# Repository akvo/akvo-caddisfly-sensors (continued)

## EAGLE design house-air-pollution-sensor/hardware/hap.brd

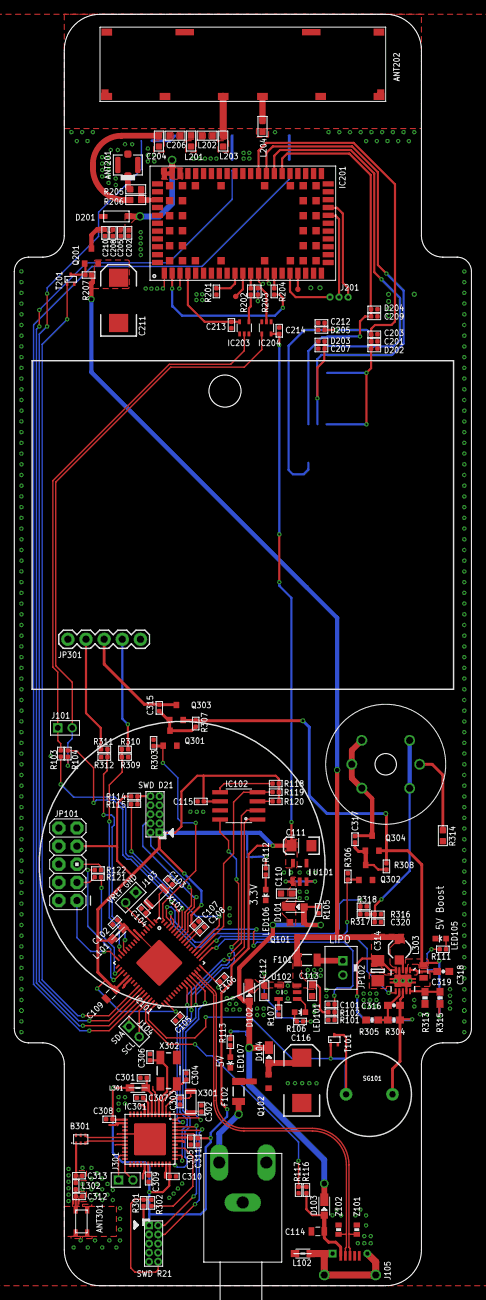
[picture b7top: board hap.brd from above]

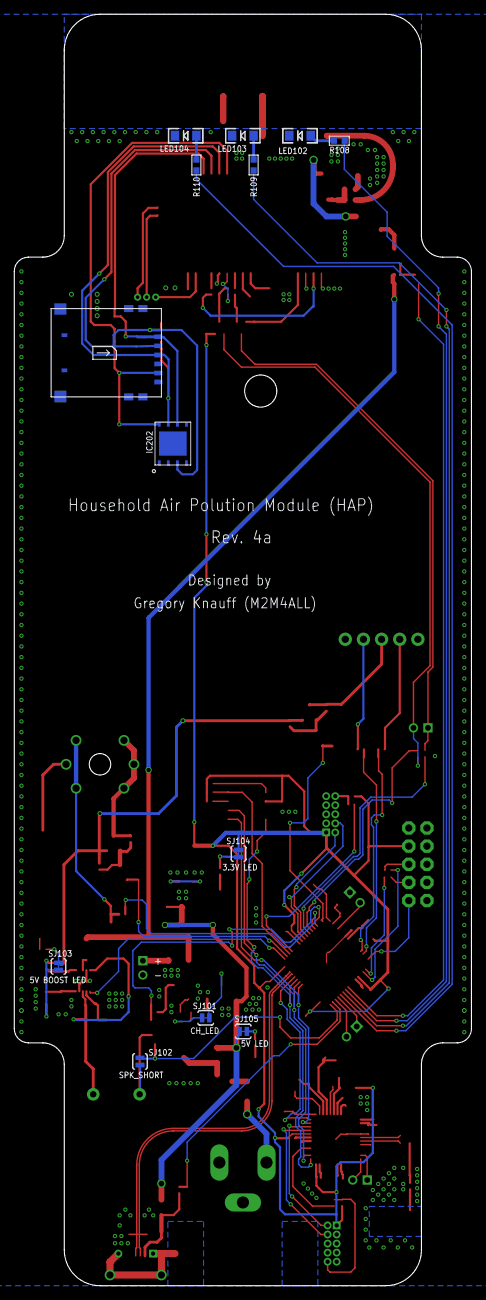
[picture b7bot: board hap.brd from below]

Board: 2 copper layers, 64.0 x 178.0 mm, 174 parts (13 on the bottom side), 124 nets.

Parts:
ANT201: 4P-U-FL
ANT202: A10393 (N.C.); A10393
ANT301: 2450AT18D0100
B301: BALUN
C101, C102, C105, C106, C107, C108, C115, C201, C210, C213, C214, C301, C305, C307, C308, C309, C310, C311, C320: 100nF; C0402
C103, C104, C202, C302, C303, C304, C306: 15pF; C0402
C109, C114, C319: 22uF; 0805
C110: 1uF; C0603
C111: 100uF; EIA3216
C112, C113: 4.7uF; C0603
C116, C211: 330uF; EIA7343
C203, C207, C209, C212: 47pF; C0402
C204: 33pF 5% (N.C.); C0603
C205: 56pF; C0402
C206: 2.2pF (+-0.1pF)(N.C.); C0603
C208: 10nF; C0402
C312: 22pF; C0402
C313: 1.2pF; C0402
C314: 10uF; 1206
C315, C317: 1uF; C0402
C316, C318: 100nF; 0603-CAP
CN101, CN301: PINHEAD-2x5-P1.27; PINHEAD_2X05_127
D101, D102, D103, D104: MSS1P2L; D1005
D201: MMSZ5231BT1G; SOD-123
D202, D203, D204, D205: PESD0402-140; R0402
F101: 0R; PTC-1206
F102: PTCSMD; PTC-1206
IC101: ATSAMD21J18-MU; QFN64
IC102: AT45DB161E; SO08
IC201: UBLOX_SARA_U2STANDARD; SARA-U2
IC202: SIM_CHIP; DFN8
IC203, IC204: 74LVC1G125DCK; SC70-5
IC301: ATSAMR21G18; QFN48_SMALL-CPAD
J101, J103, J104, J301: 2P-2.0
J105: ZX62D-B-5P8
J106: DC-005; 712-22-23_RA
J201: 1X03_1.27MM; 1X03_1.27MM_NOSILK
JP101: M05X2PTH; AVR_ICSP
JP102: JST_EPH_2PIN; JST_EPH_B2B-PH-K-S
JP301: 1X05
L101, L102, L301: MH2029-300Y; 0805
L201: 10nH 5% (N.C.); R0603
L202: 3.3nH (+-0.3nH)(N.C.); R0603
L203: N.C.; R0603
L204: 0R (N.C.); R0603
L302: 1.8nH; L0402
L303: 4.7uH, 1.2A; CDRH2D09
LED101: Yellow; LED-0603
LED102, LED103: Yellow; LED-1206
LED104: Green; LED-1206
LED105, LED106, LED107: Red; LED-0603
Q101, Q102, Q201, Q303, Q304: FDN340P; SOT23-S-PADS
Q301, Q302: 2N7002; SOT23-S-PADS
R101, R117: 4.7M; R0402
R102: 10M; R0402
R103, R106, R111, R112, R113: 1k; R0402
R104: 33R; R0402
R105, R114, R118, R119, R120, R204, R301: 100k; R0402
R107: 2k; R0402
R108, R109, R110: 220R; R0603
R115, R302: 330R; R0402
R116: 3M; R0402
R121, R122, R201, R202, R203: 0R; R0402
R205: 0R; R0603
R206: 0R (N.C.); R0603
R207, R303, R306, R307, R308: 10k; R0402
R304, R315: 2M; 0603-RES
R305, R313: 220k; 0603-RES
R309, R311, R317: 1M; R0402
R310, R312, R318: 2M; R0402
R314: 5R1; R0603
R316: 1k (DNP); R0402
SENS301: METHANE_SENSOR; MQ-3
SG101: BUZZERPTH; BUZZER-12MM
SJ101, SJ103, SJ104, SJ105: SOLDERJUMPER_NC; SJ_2S_NC
SJ102: SOLDERJUMPER_NO; SJ_2S_NO
T101, T201: DTC114YE; SC-75-3
TP1, TP2: TEST-POINT3; PAD.03X.03
U101: XC6220; SOT23-5
U102: MCP73831; SOT23-5
U201: MICRO-SIM
U301: TPS61200; QFN-10_PAD
X101, X301: 32.768 kHz; 2P-SMD-3.2X1.5
X302: 16MHz; CRYSTAL-SMD-5X3
Z101, Z102: CG0402MLC-05LG; 0402-RES

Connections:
1.8V: C213.2, IC201.4, IC203.5
3.3V: C105.2, C106.2, C107.2, C109.2, C111.A, C115.2, C214.2, C305.2, C308.2, C310.2, CN101.1, CN301.1, IC101.21, IC101.34, IC101.48, IC101.56, IC102.6, IC204.5, IC301.13, IC301.36, IC301.44, JP101.7, L101.2, L301.2, R114.1, R118.2, R119.2, R120.2, R301.1, SJ104.2, U101.5
5V: D101.+, D102.+, D103.-, D104.-, Q101.1, R105.2, SJ105.2
5V_EN: IC101.49, U301.6
+5V: C319.1, Q303.2, Q304.2, R307.2, R308.2, R315.2, SJ103.2, U301.2
BAT_VOLT: C101.2, IC101.62, R101.1, R102.2
CO2_AOUT: IC101.16, JP101.1
CO_AOUT: IC101.61, R317.2, R318.1
CO_SW: IC101.50, Q302.1, R306.2
FB: R313.2, R315.1, U301.10
GND: ANT201.GND1, ANT201.GND2, ANT201.GND3, ANT301.2, ANT301.3, ANT301.4, B301.2, B301.5, B301.6, C101.1, C102.2, C103.1, C104.2, C105.1, C106.1, C107.1, C108.1, C109.1, C110.1, C111.C, C112.2, C113.2, C114.2, C115.1, C116.C, C201.1, C202.1, C203.1, C204.2, C205.1, C207.1, C208.1, C209.1, C210.1, C211.C, C212.1, C213.1, C214.1, C301.2, C302.1, C303.2, C304.2, C305.1, C306.2, C307.2, C308.1, C309.2, C310.1, C311.2, C312.2, C313.2, C314.2, C318.2, C319.2, C320.2, CN101.3, CN101.5, CN101.9, CN301.3, CN301.5, CN301.9, D201.A, D202.2, D203.2, D204.2, D205.2, IC101.0, IC101.7, IC101.22, IC101.33, IC101.47, IC101.54, IC102.7, IC201.1, IC201.3, IC201.5, IC201.14, IC201.20, IC201.21, IC201.22, IC201.30, IC201.32, IC201.33, IC201.43, IC201.50, IC201.54, IC201.55, IC201.57, IC201.58, IC201.59, IC201.60, IC201.61, IC201.63, IC201.64, IC201.65, IC201.66, IC201.67, IC201.68, IC201.69, IC201.70, IC201.71, IC201.72, IC201.73, IC201.74, IC201.75, IC201.76, IC201.77, IC201.78, IC201.79, IC201.80, IC201.81, IC201.82, IC201.83, IC201.84, IC201.85, IC201.86, IC201.87, IC201.88, IC201.89, IC201.90, IC201.91, IC201.92, IC201.93, IC201.94, IC201.95, IC201.96, IC202.1, IC203.1, IC203.3, IC204.1, IC204.3, IC301.0, IC301.5, IC301.8, IC301.14, IC301.17, IC301.20, IC301.29, IC301.35, IC301.42, J103.1, J105.P$5, J106.SLEEVE, J106.SLEEVE_SHUNT, JP101.9, JP102.2, JP301.5, L102.1, L201.2, L203.2, L204.1, LED102.C, LED103.C, LED104.C, LED105.C, LED106.C, LED107.C, Q102.1, Q301.2, Q302.2, R102.1, R105.1, R107.2, R117.2, R201.2, R303.1, R305.1, R306.1, R310.2, R312.2, R313.1, R314.1, R316.1, R318.2, T101.2, T201.2, U101.2, U102.2, U201.C5, U201.GND@0, U201.GND@1, U201.GND@2, U201.GND@3, U201.GND@4, U201.GND@5, U301.4, U301.9, U301.11, U301.12, U301.13, U301.14, U301.15, Z101.1, Z102.1
LED1: IC101.26, R108.1
LED2: IC101.27, R109.1
LED3: IC101.28, R110.1
LIPO_STAT: LED101.C, U102.1
MISO: IC101.43, IC102.8, IC301.37
MOSI: IC101.41, IC102.1, IC301.47
unnamed: IC102.5, R118.1
unnamed: LED104.A, R110.2
unnamed: ANT301.1, C312.1, L302.1
unnamed: LED103.A, R109.2
unnamed: IC102.3, R120.1
unnamed: IC301.24, J301.2
unnamed: B301.1, C313.1, L302.2
unnamed: IC301.23, J301.1
unnamed: IC201.56, R205.2, R206.1
unnamed: F101.2, JP102.1
unnamed: C110.2, D101.-, Q101.2, U101.1, U101.3
unnamed: ANT201.D, R205.1
unnamed: LED101.A, R106.2
unnamed: R107.1, U102.5
unnamed: C112.1, D102.-, SJ101.2, U102.4
unnamed: R106.1, SJ101.1
unnamed: C204.1, C206.1, R206.2
unnamed: B301.4, IC301.18
unnamed: B301.3, IC301.19
unnamed: C206.2, L201.1, L202.1
unnamed: IC201.15, R204.1
unnamed: IC201.2, R204.2
unnamed: Q201.1, R207.2, T201.3
unnamed: IC201.10, R201.1
unnamed: IC201.11, TP1.P$1
unnamed: IC201.18, TP2.P$1
unnamed: IC201.13, R203.1
unnamed: IC201.12, R202.1
unnamed: ANT202.1, L202.2, L203.1
unnamed: C202.2, C205.2, C208.2, C210.2, D201.C, IC201.51, IC201.52, IC201.53, Q201.3
unnamed: ANT202.2, L204.2
unnamed: R314.2, SENS301.HB
unnamed: LED102.A, R108.2
unnamed: L303.P$1, U301.3
unnamed: C318.1, U301.1
unnamed: JP101.5, R122.2
unnamed: JP101.3, R121.1
unnamed: LED105.A, R111.2
unnamed: LED106.A, R112.2
unnamed: LED107.A, R113.2
unnamed: SG101.-, SJ102.1, T101.3
unnamed: IC101.32, SJ102.2, T101.1
unnamed: F102.1, J106.CENTER_PIN
unnamed: C114.1, D103.+, J105.P$1, R116.1
unnamed: C116.A, D104.+, Q102.2
unnamed: IC101.59, R103.1
unnamed: IC101.60, R104.2
unnamed: F102.2, Q102.3
unnamed: R113.1, SJ105.1
unnamed: R112.1, SJ104.1
unnamed: R111.1, SJ103.1
unnamed: C317.1, Q304.3, SENS301.A1, SENS301.A2, SENS301.HA
unnamed: C317.2, Q302.3, Q304.1, R308.1
unnamed: C315.2, Q301.3, Q303.1, R307.1
unnamed: C311.1, IC301.43
unnamed: C309.1, IC301.30
unnamed: C307.1, IC301.7
unnamed: C302.2, IC301.1, X301.1
unnamed: C303.1, IC301.2, X301.2
unnamed: C301.1, IC301.6, L301.1
unnamed: C304.1, IC301.3, X302.1
unnamed: C306.1, IC301.4, X302.3
unnamed: C315.1, JP301.3, Q303.3
unnamed: C108.2, IC101.55
unnamed: C102.1, IC101.8, L101.1
unnamed: C103.2, IC101.1, X101.1
unnamed: C104.1, IC101.2, X101.2
unnamed: C320.1, R316.2, R317.1, SENS301.B1, SENS301.B2
unnamed: JP301.4, R309.1
unnamed: JP301.2, R311.1
PM_P1: IC101.13, R311.2, R312.1
PM_P2: IC101.14, R309.2, R310.1
PM_SW: IC101.64, Q301.1, R303.2
RESETN_D21: IC101.52, R115.2
RESETN_R21: IC301.40, R302.2
RESET_D21: CN101.10, R114.2, R115.1
RESET_R21: CN301.10, R301.2, R302.1
RXD0: IC204.4, J101.2, R104.1
RXD1: IC101.18, R121.2
RXD_1V8: IC204.2, R203.2
SCK: IC101.42, IC102.2, IC301.38
SCL: IC101.30, J104.2
SDA: IC101.29, J104.1
SH1: J105.SH1, J105.SH2, J105.SH3, J105.SH4, L102.2
SIM_CLK: C209.2, D204.1, IC201.38, IC202.6, U201.C3
SIM_DATA: C212.2, D205.1, IC201.39, IC202.3, U201.C7
SIM_RST: C207.2, D203.1, IC201.40, IC202.7, U201.C2
SIM_VDD: C201.2, C203.2, D202.1, IC201.41, IC202.8, U201.C1
SS_DFLASH: IC101.51, IC102.4, R119.1
SS_R21: IC101.44, IC301.48
SWCLK_D21: CN101.4, IC101.57
SWCLK_R21: CN301.4, IC301.45
SWDIO_D21: CN101.2, IC101.58
SWDIO_R21: CN301.2, IC301.46
TXD0: IC203.2, J101.1, R103.2
TXD1: IC101.19, R122.1
TXD_1V8: IC203.4, R202.2
U2_ON: IC101.25, T201.1
USB_D+: IC201.29, J201.3
USB_D-: IC201.28, J201.2
USB_N: IC101.45, J105.P$2, Z102.2
USB_P: IC101.46, J105.P$3, Z101.2
UVLO: C316.2, R304.1, R305.2, U301.7
VBUS_DETECT: IC101.31, R116.2, R117.1
VREF: IC101.4, J103.2
VUSB: IC201.17, J201.1
V_BATT: C113.1, C211.A, C314.1, C316.1, F101.1, L303.P$2, Q101.3, Q201.2, R101.2, R207.1, R304.2, SG101.+, U102.3, U301.5, U301.8

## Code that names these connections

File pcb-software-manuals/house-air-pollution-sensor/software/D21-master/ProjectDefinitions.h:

#ifndef PROJECTDEFINITIONS_H_
#define PROJECTDEFINITIONS_H_

// ==== General
#define PROJECT_NAME "Household Air Polution Module (HAP)"

// Startup up delay so that the command prompts are not missed
#define STARTUP_DELAY 6 * 1000

// Minimum number of times to show startup commands
#define MIN_STARTUP_PROMPTS 1

// Maximum number of pages uploaded in one connection
#define MAX_PAGE_UPLOADS 16

// Minimum battery level needed to upload data (in mV)
#define MIN_BATTERY_LEVEL 3500

#define ADC_AREF 3.3f

#define BATVOLT_R1 4.7f
#define BATVOLT_R2 10.0f

// this is to make sure the firmware doesn't get stuck reading records
#define MAX_R21RECORDS_TO_READ_AT_A_TIME 16

// ==== Serial Connections
// Mandatory Streams
#define CONSOLE_STREAM SerialUSB
#define MODEM_STREAM Serial1
#define CO2_SENSOR_STREAM Serial2

// Optional Streams
#define DEBUG_STREAM SerialUSB

// Baudrates
// CONSOLE_BAUDRATE supersedes DEBUG_BAUDRATE if streams are the same
#define CONSOLE_BAUDRATE 57600
#define MODEM_BAUDRATE 57600
#define DEBUG_BAUDRATE 57600


// ==== DataFlash Segments
#define DF_SEG_CONFIG_START 0
#define DF_SEG_CONFIG_COUNT 1 // in pages

#define DF_SEG_SUM_DATA_START DF_SEG_CONFIG_COUNT
#define DF_SEG_SUM_DATA_COUNT 1024 // in pages

#define DF_SEG_SENSOR_DATA_START (DF_SEG_SUM_DATA_START + DF_SEG_SUM_DATA_COUNT)
#define DF_SEG_SENSOR_DATA_COUNT 2048 // in pages


// ==== Pins
#define BOOST_REGULATOR_ENABLE_PIN 38
#define R21_SS_PIN SS
#define DATAFLASH_SS_PIN SS_2
#define VBUS_DETECT_PIN 9
#define BATVOLT_PIN A13
#define BUZZER_PIN 10

// PM Sensor
#define PM_P1_PIN 22
#define PM_P2_PIN 21
#define PM_POWER_PIN 30

// CO Sensor
#define CO_ANALOG_PIN BAT_VOLT // 33
#define CO_POWER_PIN 39

// CO2 Sensor
#define CO2_ANALOG_PIN A10

// Modem
#define MODEM_POWER_PIN 5

// LEDs
#define LED1_PIN 6
#define LED2_PIN 7
#define LED3_PIN 8
#define SET_LED(led, on) digitalWrite(led, on)

// ==== Parameter Default Values
#define PARAM_AGGREGATION_INTERVAL (5L) // 5 mins
#define PARAM_UPLOAD_INTERVAL (60L) // 60 mins
#define PARAM_RTCSYNC_INTERVAL (24L * 60) // 24 hours


#endif /* PROJECTDEFINITIONS_H_ */

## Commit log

2017-09-19 first commit
    All files as received from SODAQ; added markdown versions of manuals, reorganized some folders
2017-09-20 Update README.md
    updated license
2017-11-29 Add design files
